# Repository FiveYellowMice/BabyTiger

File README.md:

# BabyTiger

A WiFI-enabled digital clock with 16x16 LED display. See the [blog article](https://fiveyellowmice.com/en/posts/2021/03/making-a-custom-smart-led-clock.html) I wrote for details.

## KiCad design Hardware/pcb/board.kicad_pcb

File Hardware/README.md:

3D models and PCD designs. Open them with FreeCAD and KiCad.

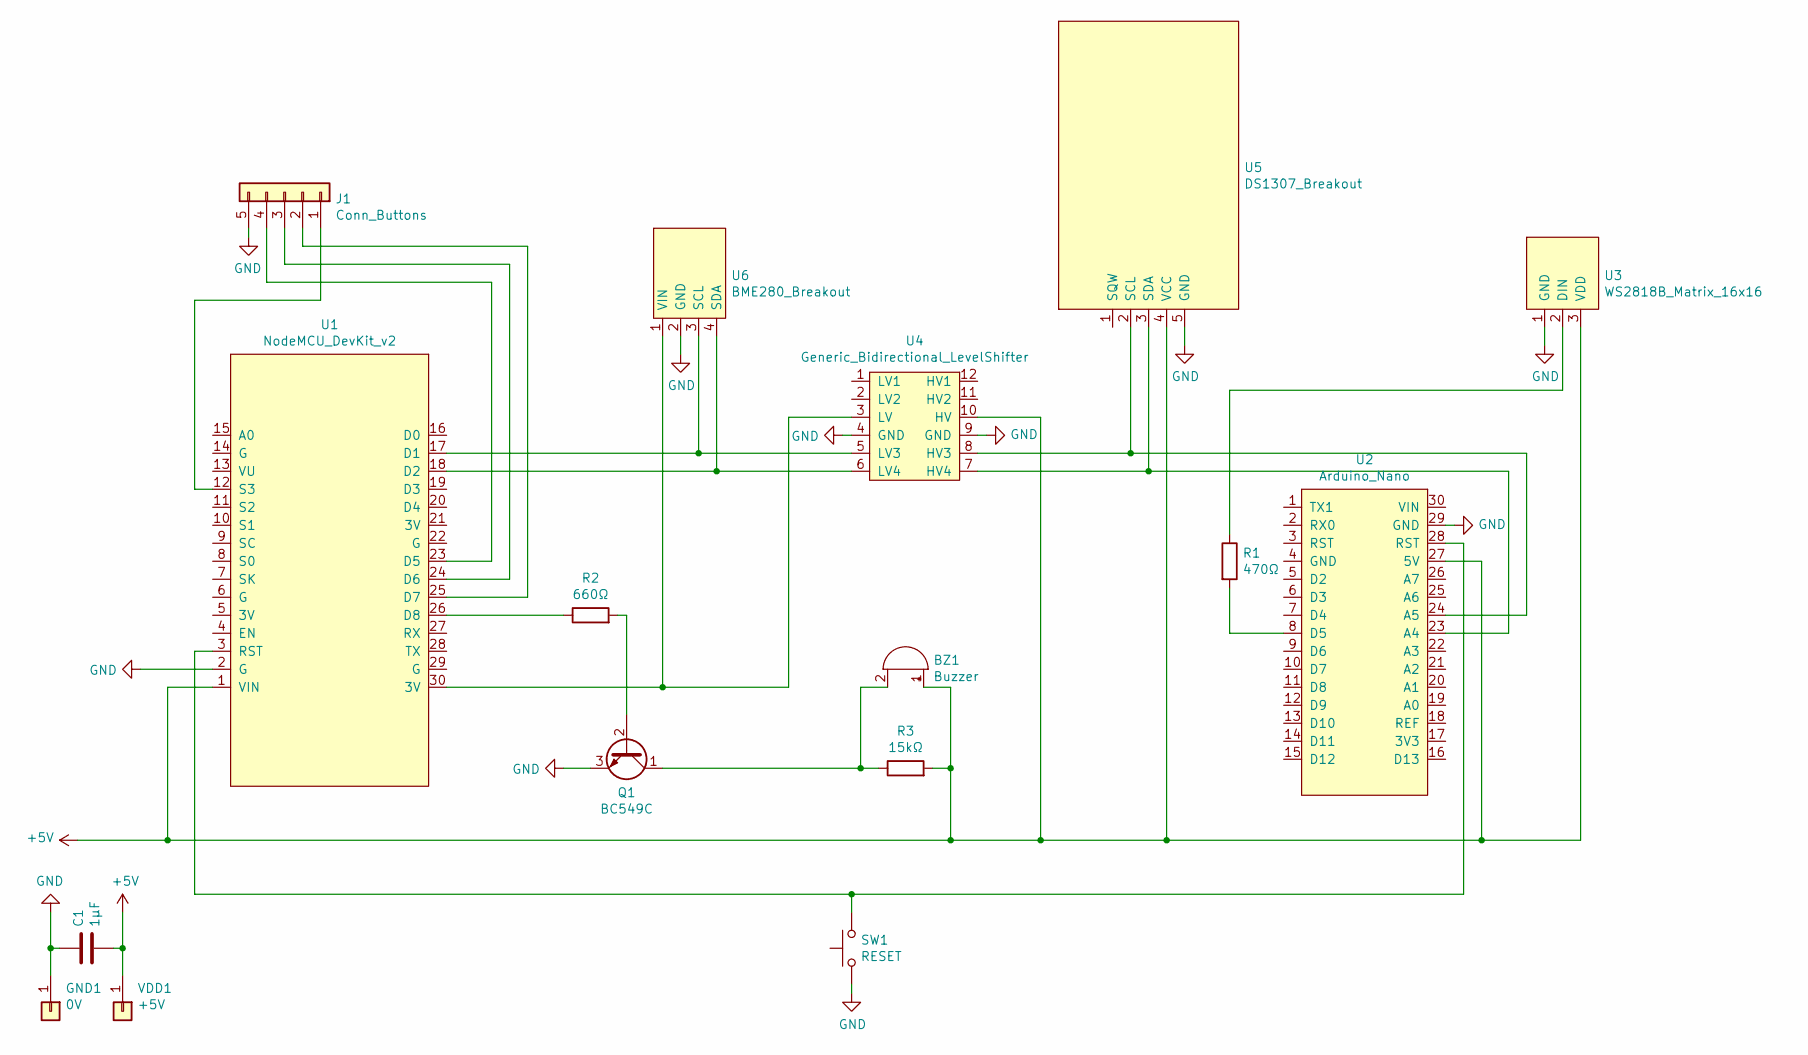
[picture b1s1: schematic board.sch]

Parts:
BZ1: Buzzer; MagneticBuzzer_ProSignal_ABT-410-RC
C1: 1µF; C_Rect_L7.0mm_W2.5mm_P5.00mm
GND1: 0V; Pin_D1.0mm_L10.0mm
J1: Conn_Buttons; PinHeader_1x05_P2.54mm_Vertical
Q1: BC549C; TO-92_Inline
R1: 470Ω; R_Axial_DIN0207_L6.3mm_D2.5mm_P10.16mm_Horizontal
R2: 660Ω; R_Axial_DIN0207_L6.3mm_D2.5mm_P10.16mm_Horizontal
R3: 15kΩ; R_Axial_DIN0207_L6.3mm_D2.5mm_P10.16mm_Horizontal
SW1: RESET; SW_PUSH_6mm
U1: NodeMCU_DevKit_v2
U2: Arduino_Nano
U3: WS2818B_Matrix_16x16; PinHeader_1x03_P2.54mm_Vertical
U4: Generic_Bidirectional_LevelShifter; DIP-12_W10.16mm
U5: DS1307_Breakout; PinHeader_1x05_P2.54mm_Vertical
U6: BME280_Breakout; PinHeader_1x04_P2.54mm_Vertical
VDD1: +5V; Pin_D1.0mm_L10.0mm

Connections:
+5V: BZ1.1 (-), C1.2, R3.2, U1.1 (VIN), U2.27 (5V), U3.3 (VDD), U4.10 (HV), U5.4 (VCC), VDD1.1
GND: C1.1, GND1.1, J1.5, Q1.3 (E), SW1.1, U1.2 (G), U2.29 (GND), U3.1 (GND), U4.4 (GND), U4.9 (GND), U5.5 (GND), U6.2 (GND)
unnamed: BZ1.2 (+), Q1.1 (C), R3.1
unnamed: J1.1, U1.12 (S3)
unnamed: J1.2, U1.25 (D7)
unnamed: J1.3, U1.24 (D6)
unnamed: J1.4, U1.23 (D5)
unnamed: Q1.2 (B), R2.2
unnamed: R1.1, U3.2 (DIN)
unnamed: R1.2, U2.8 (D5)
unnamed: R2.1, U1.26 (D8)
unnamed: SW1.2, U1.3 (RST), U2.28 (RST)
unnamed: U1.17 (D1), U4.5 (LV3), U6.3 (SCL)
unnamed: U1.18 (D2), U4.6 (LV4), U6.4 (SDA)
unnamed: U1.30 (3V), U4.3 (LV), U6.1 (VIN)
unnamed: U2.23 (A4), U4.7 (HV4), U5.3 (SDA)
unnamed: U2.24 (A5), U4.8 (HV3), U5.2 (SCL)

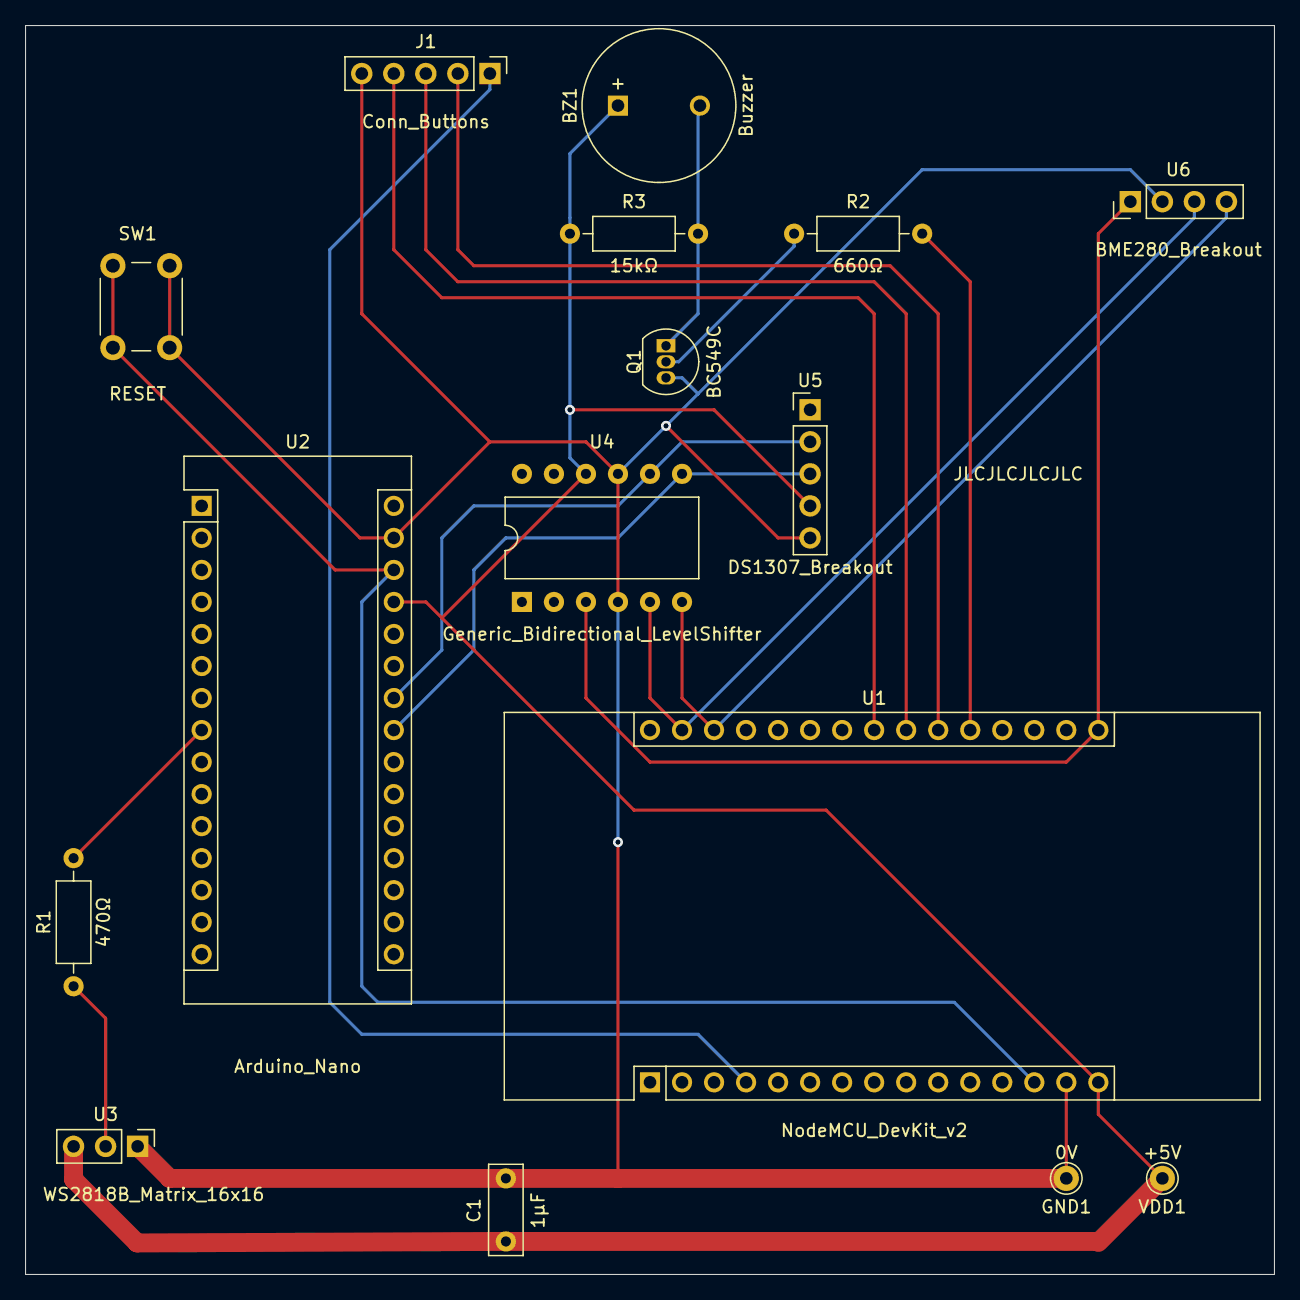
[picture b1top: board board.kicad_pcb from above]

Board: 2 copper layers, 99.1 x 99.1 mm, 16 parts (0 on the bottom side), 17 nets.

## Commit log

2021-03-20 I was stupid for not using Git this whole time
2021-03-20 Add readme and licenses
2021-04-14 babytiger_emu: Don't disable compositor
